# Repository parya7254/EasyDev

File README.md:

# EasyDev

A RP2040 Dev Board featuring 43 exposed pins along with 16 MB of flash storage! Can support up to (not recommended) 1A of power draw on VBUS! Features 29 programmable GPIO pins so that you have plenty of pins for plenty of connecting and tinkering and also a onboard NeoPixel-compatible addressable RGB LED with a exposed pin dedicated for connecting other addressable LEDs to the board without sacrificing a GPIO!

|||
|-|-|

# Why?
I was thinking of making some PCBs, and I thought, why not try something advanced and also something that you have been wanting to do for a while now? And that's when I came up with the idea of making my own RP2040 dev board (basically a Raspberry Pi Pico) starting from scratch. So I did, and learned a lot along the way! Making this devboard will definitely change the way I make PCBs in the future especially because of all the things that I learned from designing this.

# Using the EasyDev Devboard:
Using EasyDev is pretty similar to using other devboards. To use it simply connect the USB port on the devboard to your computer via a USB-C to USB-C/A cable. Then, simply write code to it like you would to a normal devboard/Arduino. To write the code, you can use CircuitPython/Micropython to program it as those are commonly used programming languages for RP2040 devboard, but if you prefer Arduino IDE, you can also use it. Then, if your program needs any connecting to external components, use 2.54mm dupont jumper wires to connect the parts to your devboard!

# Assembly:
The EasyDev devboard comes preassembled <ins>except for the header pins.</ins> You will have to solder the header pins on yourself. The max temperature recommended for soldering is 350 Degrees Celsius, but you should keep the temperature as low as possible <ins> to avoid damaging the PCB,</ins> but not too low where the solder won't properly melt and flow smoothly.

# How it Works:
If you are curious of how this devboard works, well you are in the right spot! When you connect the devboard to your computer, power goes through something called a LDO (Low Dropout Regulator) which, in our case, will keep the voltage going to the rest of the board at 3.3V. But why 3.3V, you might ask. Well, this is because the chip/microcontroller that the devboard has uses 3.3V logic and can only take 3.3V of power, your USB port has 5V of power, directly wiring the USB pins to the chip would blow it up! Then the power goes through decoupling capacitors which are like tiny batteries and then the capacitors help keep stable voltages to the RP2040 chip in case the voltage drops.  Then, there are pins on the chip called GPIOs (General Purpose Input/Output) that you can control with code. Those pins are wired to the header pins on the left and right-hand side. And then the USB data lines are also connected to the RP2040 so that the computer and the devboard can communicate with each other and to upload code to the board. And after you program the board, you can connect parts to the pins like motors, LEDs, etc. using some wires and/or a breadboard!

# PCB
||||
|-|-|-|

# Schematic

# BOM
Parts used for PCBA:
| Item # | Part Name                                   | JLC Part #    | Source | Cost (USD) | Link                                                                                                                                                 |
| -----: | :------------------------------------------ | :------------ | :----- | ---------: | :--------------------------------------------------------------------------------------------------------------------------------------------------- |
|      1 | 1uF 25V X5R ±10% 0402 MLCC Capacitor        | **C52923**    | JLCPCB |    $0.2650 | [Link](https://jlcpcb.com/partdetail/53938-CL05A105KA5NQNC/C52923)                             |
|      2 | 100nF 16V X7R ±10% 0402 MLCC Capacitor      | **C1525**     | JLCPCB |    $0.2915 | [Link](https://jlcpcb.com/partdetail/1877-CL05B104KO5NNNC/C1525)                                 |
|      3 | 10µF 10V X5R ±10% 0603 MLCC Capacitor       | **C19702**    | JLCPCB |    $0.4080 | [Link](https://jlcpcb.com/partdetail/20411-CL10A106KP8NNNC/C19702)                             |
|      4 | 33pF 50V C0G ±5% 0402 MLCC Capacitor        | **C1562**     | JLCPCB |    $0.1410 | [Link](https://jlcpcb.com/partdetail/1914-0402CG330J500NT/C1562)                                 |
|      5 | WS2812B-2020V6 RGB LED (Built-in IC)        | **C52917434** | JLCPCB |    $0.8118 | [Link](https://jlcpcb.com/partdetail/Worldsemi-WS2812B_2020V6/C52917434)                 |
|      6 | USB Type-C Connector (16P, Right Angle SMT) | **C165948**   | JLCPCB |    $0.9205 | [Link](https://jlcpcb.com/partdetail/Korean_HropartsElec-TYPE_C_31_M12/C165948)   |
|      7 | 5.1kΩ 0402 ±1% Resistor                     | **C25905**    | JLCPCB |    $0.0670 | [Link](https://jlcpcb.com/partdetail/26648-0402WGF5101TCE/C25905)                               |
|      8 | 27Ω 0402 ±1% Resistor                       | **C138021**   | JLCPCB |    $0.1034 | [Link](https://jlcpcb.com/partdetail/YAGEO-RC0402FR0727RL/C138021)                             |
|      9 | 1kΩ 0402 ±1% Resistor                       | **C11702**    | JLCPCB |    $0.0800 | [Link](https://jlcpcb.com/partdetail/12256-0402WGF1001TCE/C11702)                               |
|     10 | 10kΩ 0402 ±1% Resistor                      | **C60490**    | JLCPCB |    $0.1160 | [Link](https://jlcpcb.com/partdetail/YAGEO-RC0402FR0710KL/C60490)                               |
|     11 | 4×3mm SMT Tactile Switch                    | **C720477**   | JLCPCB |    $0.2760 | [Link](https://jlcpcb.com/partdetail/XUNPU-TS_1088AR02016/C720477)                             |
|     12 | RP2040 Microcontroller                      | **C2040**     | JLCPCB |    $4.9250 | [Link](https://jlcpcb.com/partdetail/RaspberryPi-RP2040/C2040)                                     |
|     13 | NCP1117ST33T3G 3.3V LDO Regulator           | **C26537**    | JLCPCB |    $1.1680 | [Link](https://jlcpcb.com/partdetail/onsemi-NCP1117ST33T3G/C26537)                             |
|     14 | W25Q16JVUXIQ 16Mbit SPI Flash               | **C2843335**  | JLCPCB |   $10.1720 | [Link](https://jlcpcb.com/partdetail/WinbondElec-W25Q16JVUXIQ/C2843335)                   |
|     15 | 12MHz SMD Crystal                           | **C9002**     | JLCPCB |    $0.4750 | [Link](https://jlcpcb.com/partdetail/YXC_CrystalOscillators-X322512MSB4SI/C9002) |
|16|PCB and PCBA cost|-|JLCPCB|$25|https://jlcpcb.com"|
| - | Total Cost | - | - | $45.22 | - |

[//]: # ( # OLD PCB!!

)

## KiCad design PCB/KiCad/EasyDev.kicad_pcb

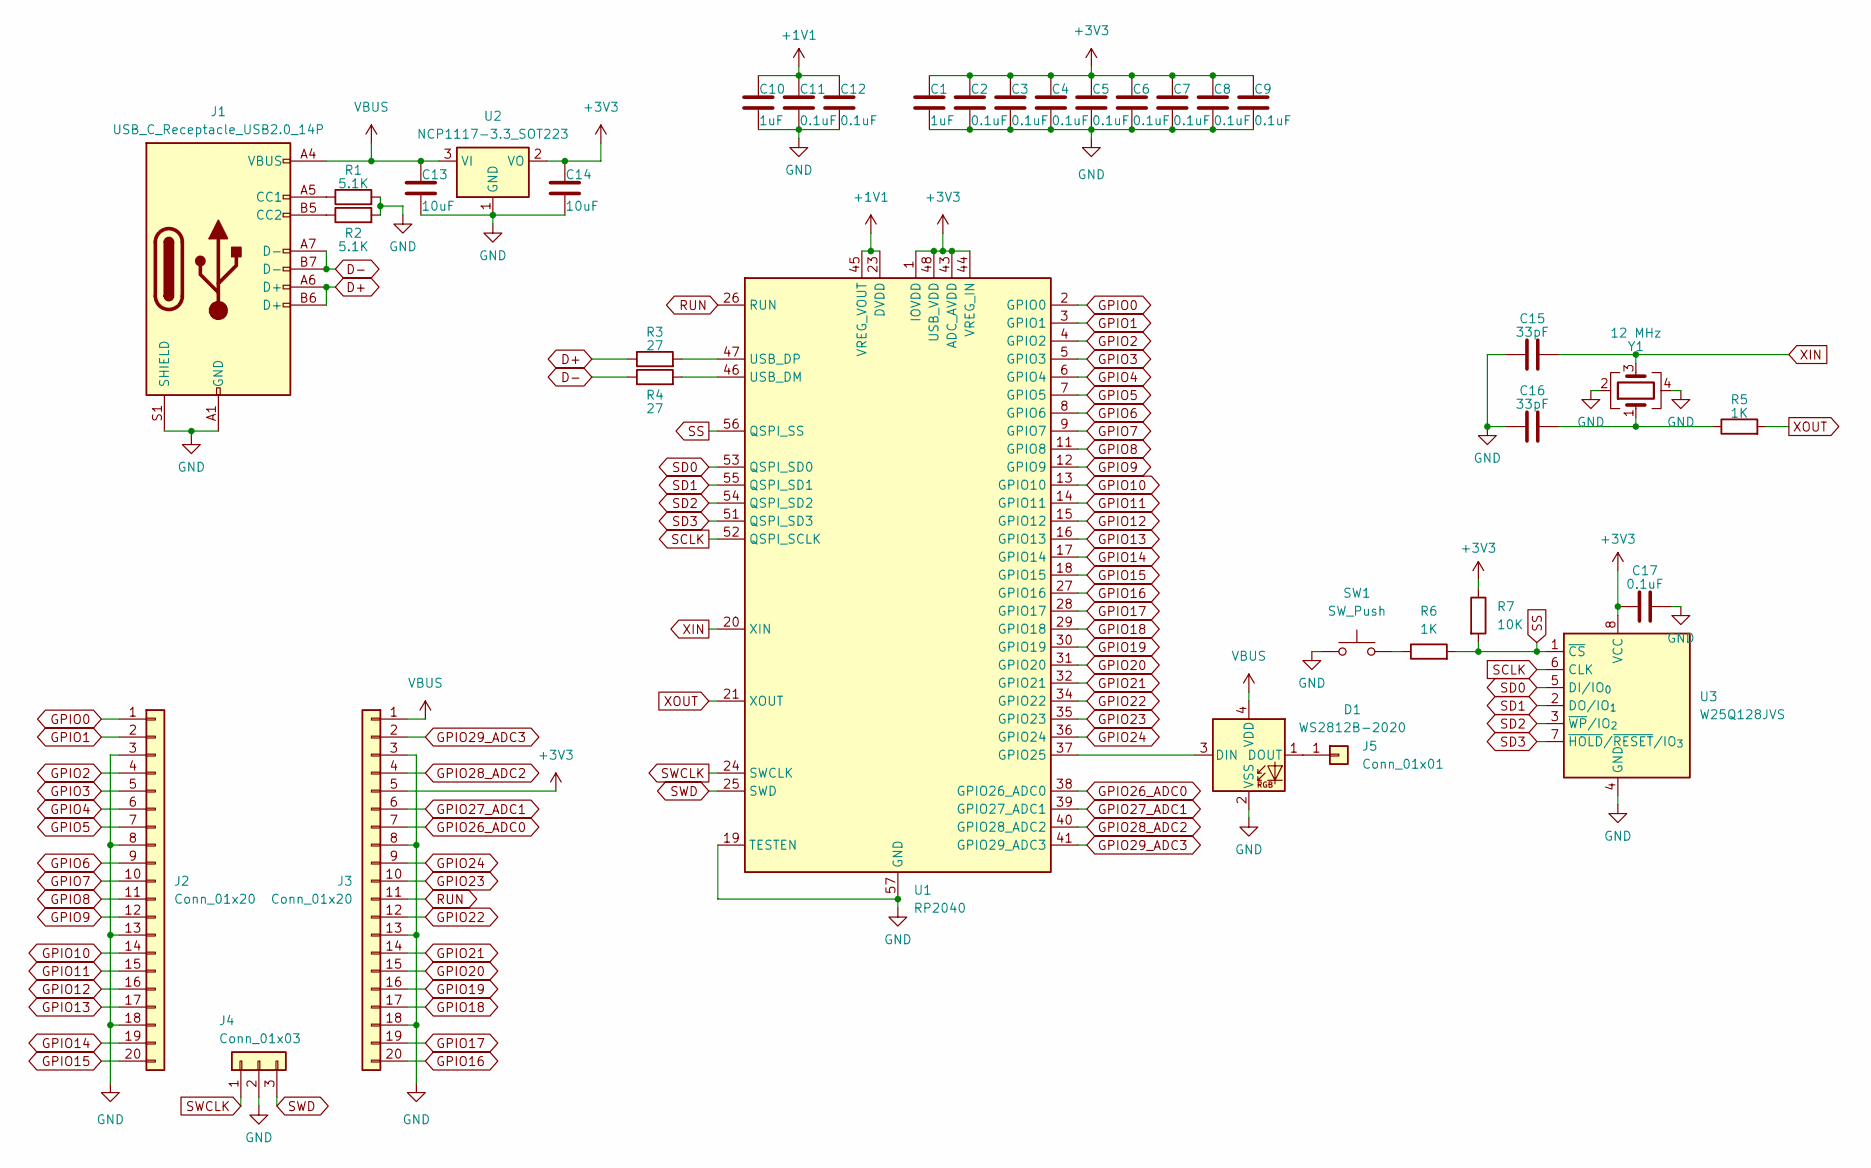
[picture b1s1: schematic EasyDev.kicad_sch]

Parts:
C1, C10: 1uF; C_0402_1005Metric
C2, C3, C4, C5, C6, C7, C8, C9, C11, C12, C17: 0.1uF; C_0402_1005Metric
C13, C14: 10uF; C_0603_1608Metric
C15, C16: 33pF; C_0402_1005Metric
D1: WS2812B-2020; LED_WS2812B-2020_PLCC4_2.0x2.0mm
J1: USB_C_Receptacle_USB2.0_14P; USB_C_Receptacle_HRO_TYPE-C-31-M-12
J2, J3: Conn_01x20; PinSocket_1x20_P2.54mm_Vertical
J4: Conn_01x03; PinSocket_1x03_P2.54mm_Vertical
J5: Conn_01x01; PinSocket_1x01_P2.54mm_Vertical
R1, R2: 5.1K; R_0402_1005Metric
R3, R4: 27; R_0402_1005Metric
R5, R6: 1K; R_0402_1005Metric
R7: 10K; R_0402_1005Metric
SW1: SW_Push; SW_Push_SPST_NO_Alps_SKRK
U1: RP2040; QFN-56-1EP_7x7mm_P0.4mm_EP3.2x3.2mm
U2: NCP1117-3.3_SOT223; SOT-223-3_TabPin2
U3: W25Q128JVS; Winbond_USON-8-1EP_3x2mm_P0.5mm_EP0.2x1.6mm
Y1: 12 MHz; Crystal_SMD_3225-4Pin_3.2x2.5mm

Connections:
+1V1: C10.1, C11.1, C12.1, U1.23 (DVDD), U1.45 (VREG_VOUT), U1.50 (DVDD)
+3V3: C1.1, C2.1, C3.1, C4.1, C5.1, C6.1, C7.1, C8.1, C9.1, C14.1, C17.1, J3.5, R7.1, U1.1 (IOVDD), U1.10 (IOVDD), U1.22 (IOVDD), U1.33 (IOVDD), U1.42 (IOVDD), U1.43 (ADC_AVDD), U1.44 (VREG_IN), U1.48 (USB_VDD), U1.49 (IOVDD), U2.2 (VO), U3.8 (VCC)
D+: J1.A6 (D+), J1.B6 (D+), R3.1
D-: J1.A7 (D-), J1.B7 (D-), R4.1
GND: C1.2, C2.2, C3.2, C4.2, C5.2, C6.2, C7.2, C8.2, C9.2, C10.2, C11.2, C12.2, C13.2, C14.2, C15.1, C16.1, C17.2, D1.2 (VSS), J1.A1 (GND), J1.A12 (GND), J1.B1 (GND), J1.B12 (GND), J1.S1 (SHIELD), J2.3, J2.8, J2.13, J2.18, J3.3, J3.8, J3.13, J3.18, J4.2, R1.2, R2.2, SW1.1, U1.19 (TESTEN), U1.57 (GND), U2.1 (GND), U3.4 (GND), Y1.2, Y1.4
GPIO0: J2.1, U1.2 (GPIO0)
GPIO1: J2.2, U1.3 (GPIO1)
GPIO2: J2.4, U1.4 (GPIO2)
GPIO3: J2.5, U1.5 (GPIO3)
GPIO4: J2.6, U1.6 (GPIO4)
GPIO5: J2.7, U1.7 (GPIO5)
GPIO6: J2.9, U1.8 (GPIO6)
GPIO7: J2.10, U1.9 (GPIO7)
GPIO8: J2.11, U1.11 (GPIO8)
GPIO9: J2.12, U1.12 (GPIO9)
GPIO10: J2.14, U1.13 (GPIO10)
GPIO11: J2.15, U1.14 (GPIO11)
GPIO12: J2.16, U1.15 (GPIO12)
GPIO13: J2.17, U1.16 (GPIO13)
GPIO14: J2.19, U1.17 (GPIO14)
GPIO15: J2.20, U1.18 (GPIO15)
GPIO16: J3.20, U1.27 (GPIO16)
GPIO17: J3.19, U1.28 (GPIO17)
GPIO18: J3.17, U1.29 (GPIO18)
GPIO19: J3.16, U1.30 (GPIO19)
GPIO20: J3.15, U1.31 (GPIO20)
GPIO21: J3.14, U1.32 (GPIO21)
GPIO22: J3.12, U1.34 (GPIO22)
GPIO23: J3.10, U1.35 (GPIO23)
GPIO24: J3.9, U1.36 (GPIO24)
GPIO26_ADC0: J3.7, U1.38 (GPIO26_ADC0)
GPIO27_ADC1: J3.6, U1.39 (GPIO27_ADC1)
GPIO28_ADC2: J3.4, U1.40 (GPIO28_ADC2)
GPIO29_ADC3: J3.2, U1.41 (GPIO29_ADC3)
unnamed: C16.2, R5.1, Y1.1
unnamed: D1.3 (DIN), U1.37 (GPIO25)
unnamed: D1.1 (DOUT), J5.1
unnamed: J1.A5 (CC1), R1.1
unnamed: J1.B5 (CC2), R2.1
unnamed: R6.1, SW1.2
unnamed: R4.2, U1.46 (USB_DM)
unnamed: R3.2, U1.47 (USB_DP)
RUN: J3.11, U1.26 (RUN)
SCLK: U1.52 (QSPI_SCLK), U3.6 (CLK)
SD0: U1.53 (QSPI_SD0), U3.5 (DI/IO_{0})
SD1: U1.55 (QSPI_SD1), U3.2 (DO/IO_{1})
SD2: U1.54 (QSPI_SD2), U3.3 (~WP/IO_{2})
SD3: U1.51 (QSPI_SD3), U3.7 (~HOLD/~RESET/IO_{3})
SS: R6.2, R7.2, U1.56 (QSPI_SS), U3.1 (~CS)
SWCLK: J4.1, U1.24 (SWCLK)
SWD: J4.3, U1.25 (SWD)
VBUS: C13.1, D1.4 (VDD), J1.A4 (VBUS), J1.A9 (VBUS), J1.B4 (VBUS), J1.B9 (VBUS), J3.1, U2.3 (VI)
XIN: C15.2, U1.20 (XIN), Y1.3
XOUT: R5.2, U1.21 (XOUT)

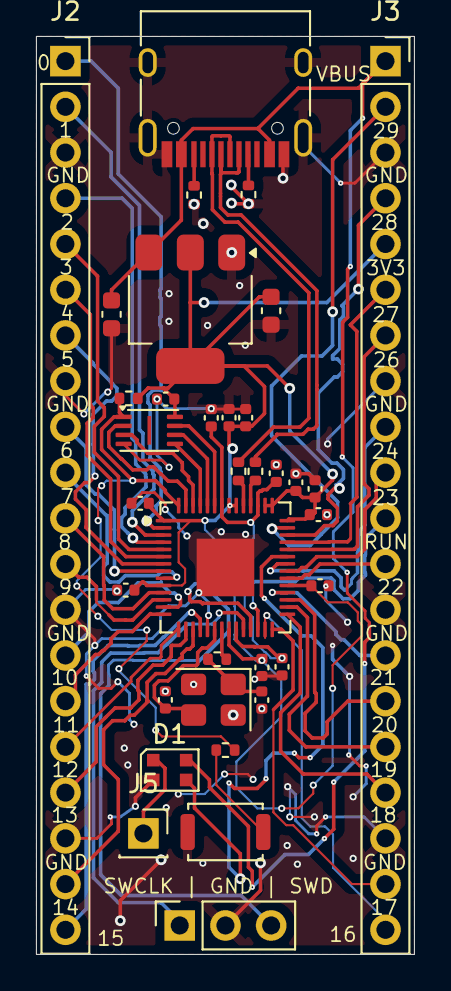
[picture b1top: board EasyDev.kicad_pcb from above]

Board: 2 copper layers, 21.0 x 51.0 mm, 35 parts (0 on the bottom side), 54 nets.

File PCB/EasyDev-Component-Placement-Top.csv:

Ref,Val,Package,PosX,PosY,Rot,Side
"C1","1uF","C_0402_1005Metric",168.094790,-79.406673,90.000000,top
"C2","0.1uF","C_0402_1005Metric",165.140138,-89.325087,-90.000000,top
"C3","0.1uF","C_0402_1005Metric",158.379481,-80.206715,180.000000,top
"C4","0.1uF","C_0402_1005Metric",168.368721,-84.788945,0.000000,top
"C5","0.1uF","C_0402_1005Metric",168.277812,-80.837647,0.000000,top
"C6","0.1uF","C_0402_1005Metric",157.577919,-85.032096,180.000000,top
"C7","0.1uF","C_0402_1005Metric",164.240059,-75.451954,90.000000,top
"C8","0.1uF","C_0402_1005Metric",167.029762,-79.041389,90.000000,top
"C9","0.1uF","C_0402_1005Metric",163.314044,-75.449777,90.000000,top
"C10","1uF","C_0402_1005Metric",166.258185,-89.291561,-90.000000,top
"C11","0.1uF","C_0402_1005Metric",165.937724,-78.540642,90.000000,top
"C12","0.1uF","C_0402_1005Metric",162.328472,-75.459162,90.000000,top
"C13","10uF","C_0603_1608Metric",156.786707,-69.710370,-90.000000,top
"C14","10uF","C_0603_1608Metric",165.649569,-69.510029,-90.000000,top
"C15","33pF","C_0402_1005Metric",159.777743,-91.129262,-90.000000,top
"C16","33pF","C_0402_1005Metric",165.134333,-91.138788,90.000000,top
"C17","0.1uF","C_0402_1005Metric",159.792875,-74.418061,180.000000,top
"D1","WS2812B-2020","LED_WS2812B-2020_PLCC4_2.0x2.0mm",160.018639,-95.028324,0.000000,top
"J1","USB_C_Receptacle_USB2.0_14P","USB_C_Receptacle_HRO_TYPE-C-31-M-12",163.115625,-56.771875,180.000000,top
"J2","Conn_01x20","PinSocket_1x20_P2.54mm_Vertical",154.225625,-55.641875,0.000000,top
"J3","Conn_01x20","PinSocket_1x20_P2.54mm_Vertical",172.005625,-55.641875,0.000000,top
"J4","Conn_01x03","PinSocket_1x03_P2.54mm_Vertical",160.575625,-103.661875,90.000000,top
"J5","Conn_01x01","PinSocket_1x01_P2.54mm_Vertical",158.557827,-98.548552,0.000000,top
"R1","5.1K","R_0402_1005Metric",164.394777,-63.058838,-90.000000,top
"R2","5.1K","R_0402_1005Metric",161.373806,-63.082210,-90.000000,top
"R3","27","R_0402_1005Metric",163.840607,-78.431261,-90.000000,top
"R4","27","R_0402_1005Metric",164.780607,-78.431261,-90.000000,top
"R5","1K","R_0402_1005Metric",162.652626,-88.870549,0.000000,top
"R6","1K","R_0402_1005Metric",163.115625,-93.918125,0.000000,top
"R7","10K","R_0402_1005Metric",157.736536,-74.379629,180.000000,top
"SW1","SW_Push","SW_Push_SPST_NO_Alps_SKRK",163.115625,-98.469375,0.000000,top
"U1","RP2040","QFN-56-1EP_7x7mm_P0.4mm_EP3.2x3.2mm",163.115625,-83.771875,0.000000,top
"U2","NCP1117-3.3_SOT223","SOT-223-3_TabPin2",161.163319,-69.426151,-90.000000,top
"U3","W25Q128JVS","Winbond_USON-8-1EP_3x2mm_P0.5mm_EP0.2x1.6mm",158.883718,-76.158379,0.000000,top
"Y1","12 MHz","Crystal_SMD_3225-4Pin_3.2x2.5mm",162.446271,-91.119341,180.000000,top
